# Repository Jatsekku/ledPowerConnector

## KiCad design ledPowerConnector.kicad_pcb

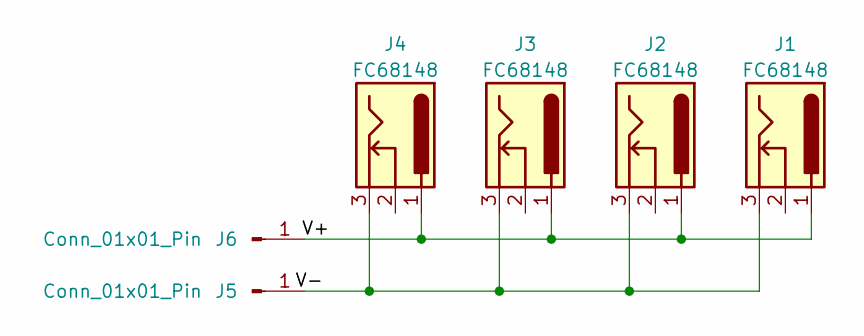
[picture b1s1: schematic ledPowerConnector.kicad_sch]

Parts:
J1, J2, J3, J4: FC68148; BarrelJack_GCT_DCJ200-10-A_Horizontal
J5, J6: Conn_01x01_Pin; Pin_D1.1mm_L8.5mm_W2.5mm_FlatFork

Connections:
/V+: J1.1, J2.1, J3.1, J4.1, J6.1
/V-: J1.3, J2.3, J3.3, J4.3, J5.1

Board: 2 copper layers, 6 parts (0 on the bottom side), 2 nets, no tracks yet.

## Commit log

2024-12-30 feat: Add initial readme
2024-12-30 feat(sch): Add schematic
2024-12-30 feat(pcb): Add PCB layout
2024-12-30 feat(gerbers): Add gerbers output
